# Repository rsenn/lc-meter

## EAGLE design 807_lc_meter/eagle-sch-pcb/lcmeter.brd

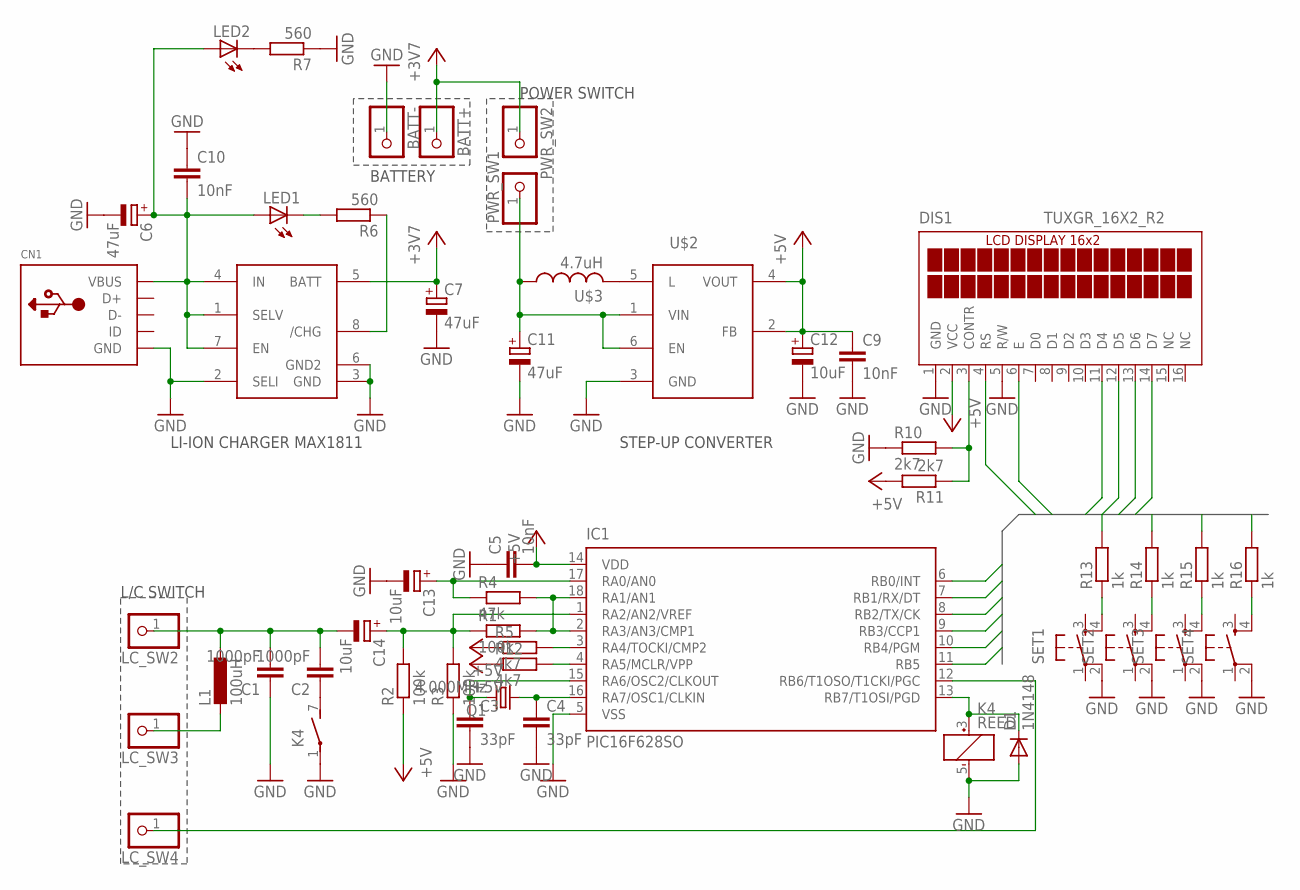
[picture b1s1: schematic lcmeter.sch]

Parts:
BATT+: PINHD-1X1; 1X01
BATT-: PINHD-1X1; 1X01
C1, C2: 1000pF; C0805
C3, C4: 33pF; C0805
C5, C9, C10: 10nF; C0805
C6, C7, C11: 47uF; B/3528-21W
C12, C13, C14: 10uF; B/3528-21W
CN1: USBMINIB; USB-MINIB
D1: 1N4148; MINIMELF
DIS1: TUXGR_16X2_R2
IC1: PIC16F628SO; SO-18W
K4: REED
L1: 100uH; 0204/5
LC_SW2, LC_SW3, LC_SW4: PINHD-1X1; 1X01
LED1, LED2: LED1206; LED-1206
PWR_SW1, PWR_SW2: PINHD-1X1; 1X01
Q1: 4.000MHz; CRYSTAL_SM49
R1, R2, R3: 100k; R0603
R4: 47k; R0603
R5, R12: 4k7; R0603
R6, R7: 560; R0603
R10, R11: 2k7; R0603
R13, R14, R15, R16: 1k; R0603
SET1, SET2, SET3, SET4: TAC_SWITCHPTH; TACTILE-PTH
U$1: MAX1811SO8; SO08
U$2: TPS6122XSOT-6; SOT23-6
U$3: 4.7uH; EPL3015

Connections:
+3V3: BATT+.1, C7.+, PWR_SW2.1, U$1.5 (BATT)
+5V: C5.2, C9.1, C12.+, DIS1.2 (VCC), IC1.14 (VDD), R2.1, R5.1, R11.2, R12.1, U$2.2 (FB), U$2.4 (VOUT)
GND: BATT-.1, C1.1, C3.2, C4.2, C5.1, C6.-, C7.-, C9.2, C10.1, C11.-, C12.-, C13.-, CN1.GND, D1.A, DIS1.1 (GND), DIS1.5 (R/W), IC1.5 (VSS), K4.1, K4.5 (-), R3.1, R7.1, R10.1, SET1.2, SET2.2, SET3.2, SET4.2, U$1.2 (SELI), U$1.3 (GND), U$1.6 (GND2), U$2.3 (GND)
LCDPIN0: DIS1.4 (RS), IC1.6 (RB0/INT)
LCDPIN1: DIS1.6 (E), IC1.7 (RB1/RX/DT)
LCDPIN2: DIS1.11 (D4), IC1.8 (RB2/TX/CK), R13.2
LCDPIN3: DIS1.12 (D5), IC1.9 (RB3/CCP1), R14.2
LCDPIN4: DIS1.13 (D6), IC1.11 (RB5), R15.2
LCDPIN5: DIS1.14 (D7), IC1.10 (RB4/PGM), R16.2
unnamed: C13.+, IC1.17 (RA0/AN0), R4.1
unnamed: IC1.2 (RA3/AN3/CMP1), IC1.18 (RA1/AN1), R1.2, R4.2
unnamed: C14.+, IC1.1 (RA2/AN2/VREF), R1.1, R2.2, R3.2
unnamed: C1.2, C2.2, C14.-, L1.1, LC_SW2.1
unnamed: DIS1.3 (CONTR), R10.2, R11.1
unnamed: C2.1, K4.7 (S)
unnamed: IC1.3 (RA4/TOCKI/CMP2), R5.2
unnamed: IC1.12 (RB6/T1OSO/T1CKI/PGC), LC_SW4.1
unnamed: C4.1, IC1.16 (RA7/OSC1/CLKIN), Q1.1
unnamed: C3.1, IC1.15 (RA6/OSC2/CLKOUT), Q1.2
unnamed: D1.C, IC1.13 (RB7/T1OSI/PGD), K4.3 (+)
unnamed: R13.1, SET1.4
unnamed: R14.1, SET2.4
unnamed: R15.1, SET3.4
unnamed: R16.1, SET4.4
unnamed: IC1.4 (RA5/MCLR/VPP), R12.2
unnamed: L1.2, LC_SW3.1
unnamed: C6.+, C10.2, CN1.VBUS, LED1.A, LED2.A, U$1.1 (SELV), U$1.4 (IN), U$1.7 (EN)
unnamed: U$2.5 (L), U$3.P$2 (2)
unnamed: LED1.C, R6.2
unnamed: R6.1, U$1.8 (/CHG)
unnamed: C11.+, PWR_SW1.1, U$2.1 (VIN), U$2.6 (EN), U$3.P$1 (1)
unnamed: LED2.C, R7.2

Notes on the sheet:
POWER SWITCH
BATTERY
L/C SWITCH
STEP-UP CONVERTER
LI-ION CHARGER MAX1811

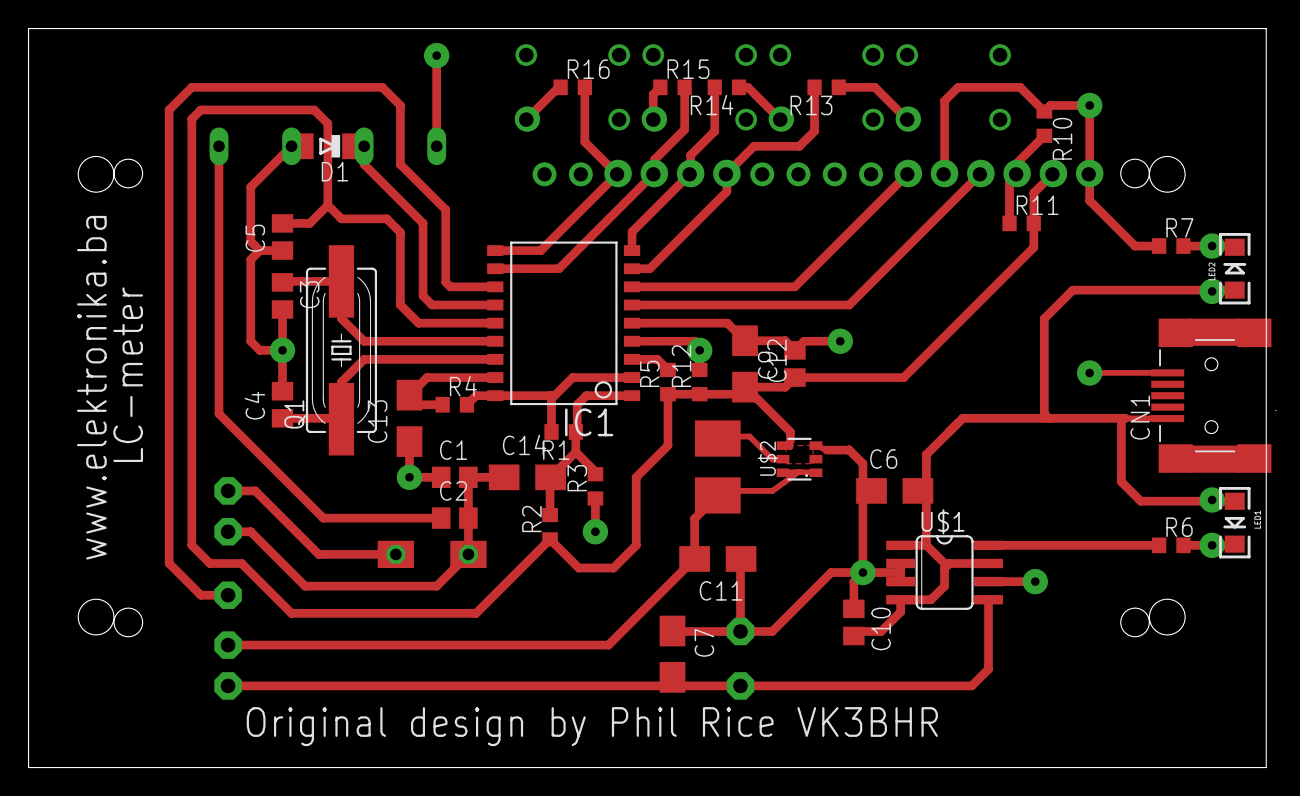
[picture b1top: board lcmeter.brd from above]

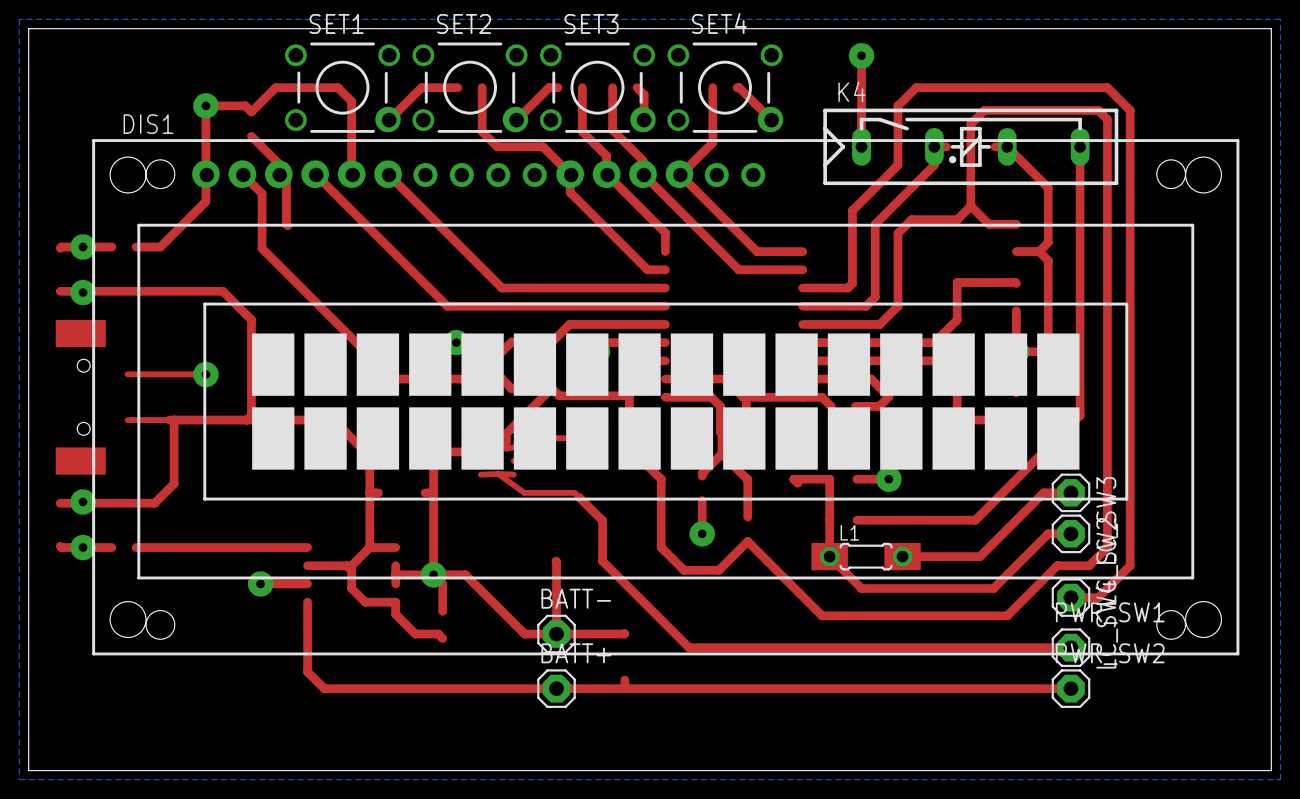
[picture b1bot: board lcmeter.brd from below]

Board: 2 copper layers, 86.7 x 51.7 mm, 50 parts (14 on the bottom side), 32 nets.

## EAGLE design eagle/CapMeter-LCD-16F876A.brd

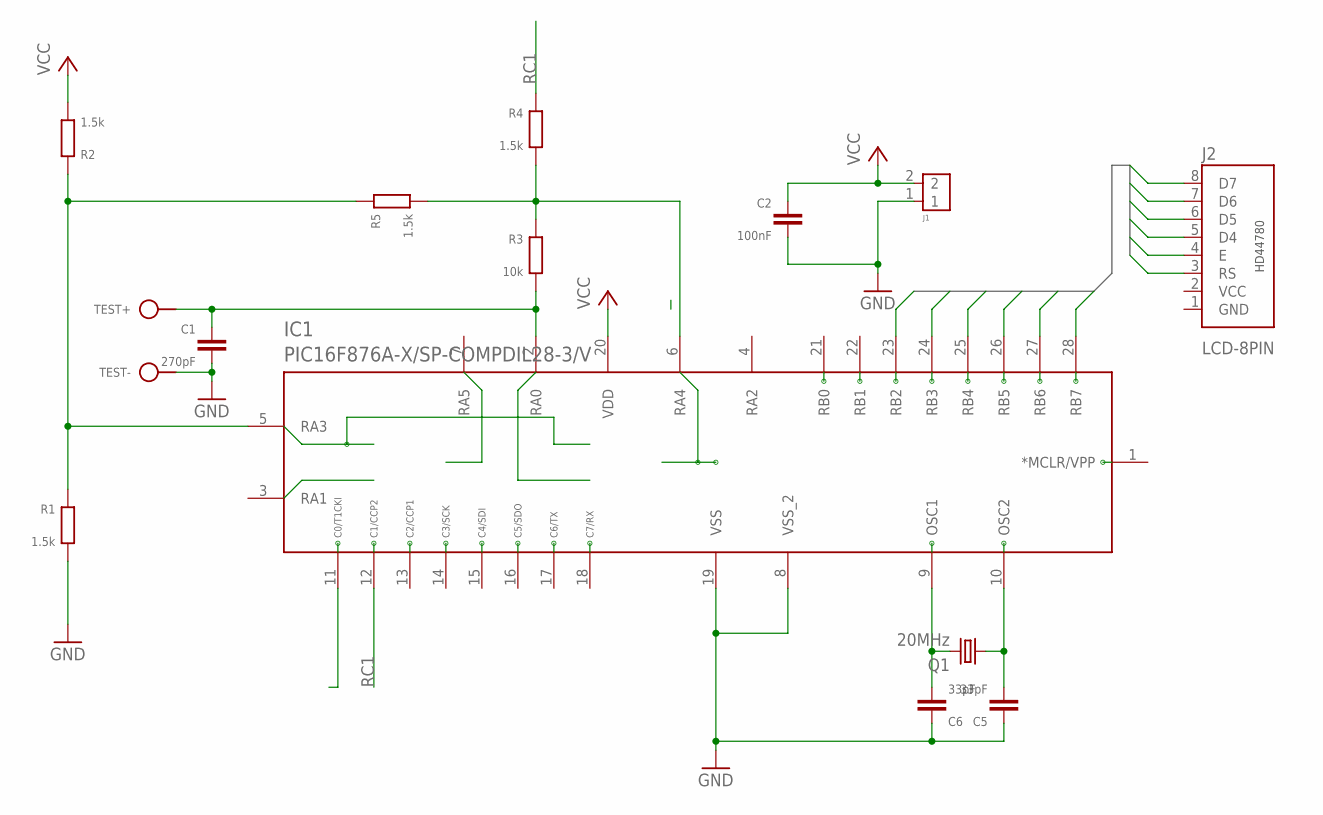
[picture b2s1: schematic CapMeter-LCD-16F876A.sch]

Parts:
C1: 270pF; C050-020X036
C2: 100nF; C025-020X036
C5, C6: 33pF; C025-020X036
IC1: PIC16F876A-X/SP-COMPDIL28-3/V; DIL28-3/V
J1: CONN-2P2P/H; CONN-2P
J2: LCD-8PIN; 1X8
Q1: 20MHz; HC49
R1, R2, R4, R5: 1.5k; 0204/10
R3: 10k; 0204/10
TEST+: SPAD
TEST-: SPAD

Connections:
D4: IC1.25 (RB4), J2.5 (D4)
D5: IC1.26 (RB5), J2.6 (D5)
D6: IC1.27 (RB6), J2.7 (D6)
D7: IC1.28 (RB7), J2.8 (D7)
E: IC1.24 (RB3), J2.4 (E)
GND: C1.2, C2.2, C5.1, C6.1, IC1.8 (VSS_2), IC1.19 (VSS), J1.1, R1.1, TEST-.1
unnamed: C1.1, IC1.2 (RA0), R3.1, TEST+.1
unnamed: IC1.6 (RA4), R3.2, R4.1, R5.1
unnamed: IC1.5 (RA3), R1.2, R2.2, R5.2
OSC1: C6.2, IC1.9 (OSC1), Q1.2
OSC2: C5.2, IC1.10 (OSC2), Q1.1
RC1: IC1.12 (RC1), R4.2
RS: IC1.23 (RB2), J2.3 (RS)
VCC: C2.1, IC1.20 (VDD), J1.2, R2.1

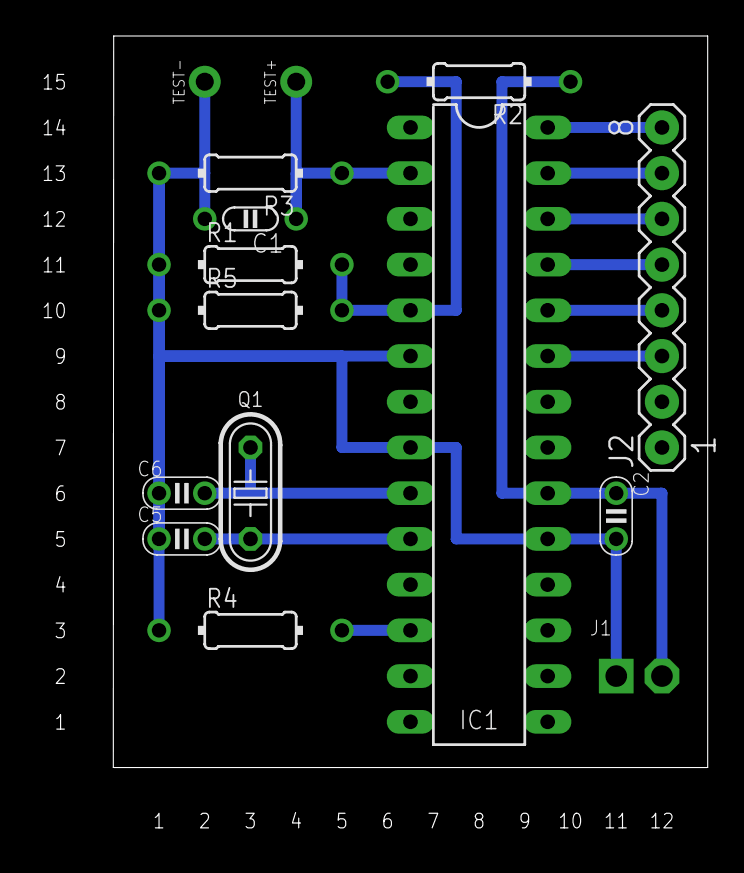
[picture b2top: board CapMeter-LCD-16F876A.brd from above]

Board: 2 copper layers, 33.0 x 40.6 mm, 15 parts (0 on the bottom side), 14 nets.

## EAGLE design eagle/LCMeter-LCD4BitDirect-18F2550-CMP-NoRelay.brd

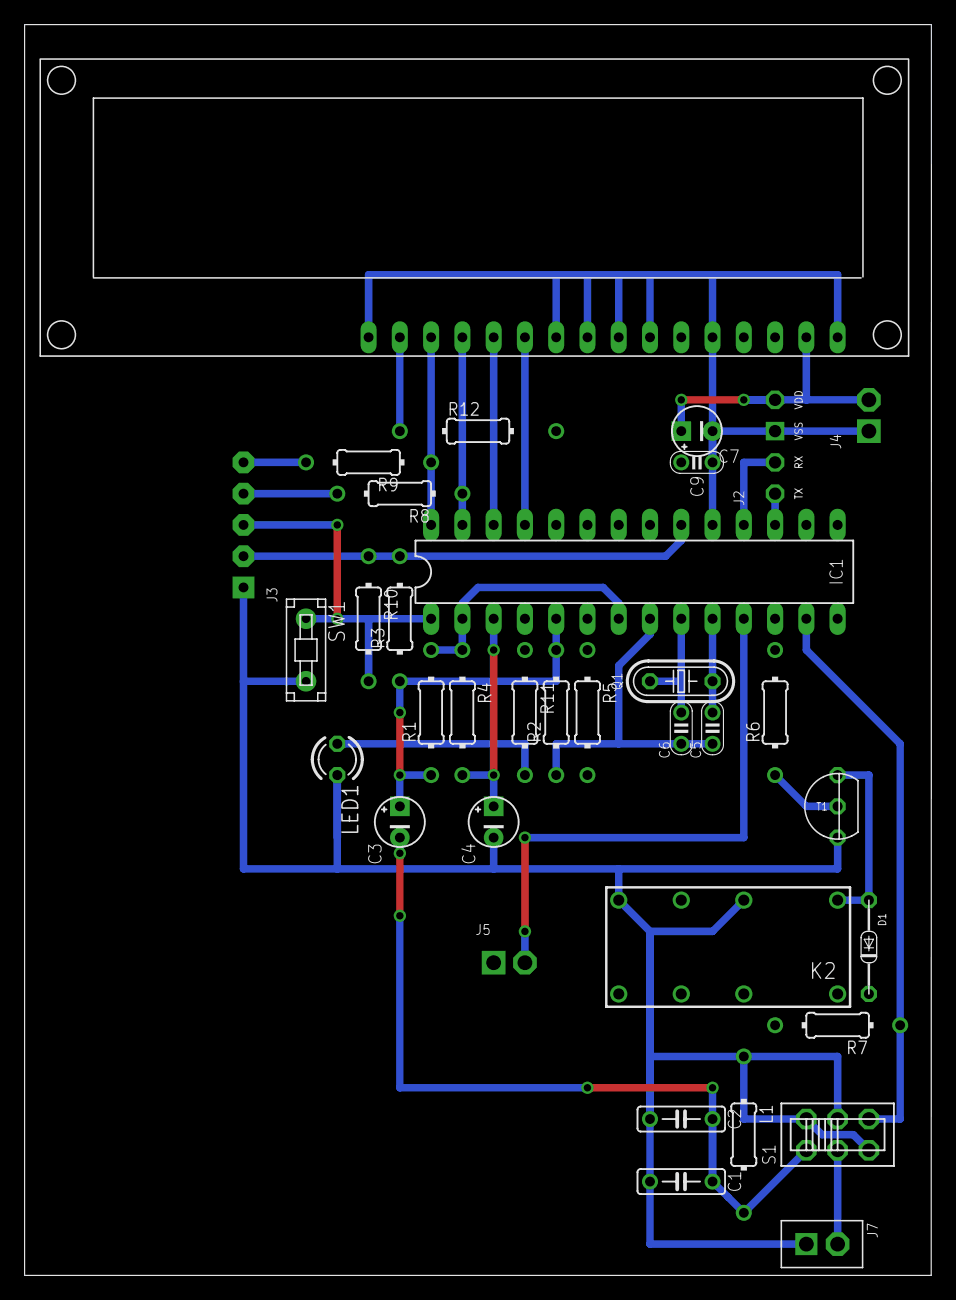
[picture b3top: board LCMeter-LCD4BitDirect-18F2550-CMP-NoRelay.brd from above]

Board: 2 copper layers, 73.7 x 101.6 mm, 35 parts (0 on the bottom side), 31 nets.

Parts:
C1, C2: 1nF; C050-025X060
C3, C4: 10μF; E2,5-4
C5, C6: 15pF; C025-020X036
C7: 100μF; E2,5-4
C9: 100nF; C025-020X036/V
D1: 1N4148; DO34-7
IC1: PIC18F2550-I/SP-COMP-B-V; DIL28-3/V
J2: PIC-UART
J3: PIC-ICSP
J4: PWR; CONN-2P
J5: FREQ; CONN-2P
J7: TEST-LC; CONN-2P-V
K2: DS2Y
L1: 82μH; 0204/12
LCD: HD44780LM016L; LM016L-HD44780
LED1: TLLG4400; LED3MM
Q1: 20MHz; HC49
R1, R2, R3: 100k; 0204/10
R4: 47k; 0204/10-V
R5, R10: 4.7k; 0204/10
R6, R7: 10k; 0204/10-V
R8, R9: 100; 0204/10-V
R11: 1k; 0204/10-V
R12: 330; 0204/12
S1: SL-SW-2P-2T; SLSW-2P2T
SW1: PB-1P-1T; PB-1P1T
T1: 2N3904; TO92

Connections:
/LC: IC1.13, R7.2, S1.6
/MCLR: IC1.1, J3.3, R10.2, SW1.2
/RELAY: IC1.12, R6.1
/RX: IC1.18, J2.18
/TX: IC1.17, J2.17
A0: IC1.2, IC1.7, R1.2, R4.2
A1: C4.+, IC1.3, R4.1
A3: C3.+, IC1.5, R1.1, R2.2, R3.1
A4: IC1.6, R5.1
C2_CON: C2.2, K2.4
D4: IC1.25, LCD.11
D5: IC1.26, LCD.12
D6: IC1.27, LCD.13, R8.2
D7: IC1.28, LCD.14, R9.2
E: IC1.24, LCD.6
FREQ: IC1.11, J5.2
GND: C1.2, C4.-, C5.1, C6.1, C7.-, C9.1, IC1.8, IC1.19, J2.19, J3.1, J4.1, J5.1, J7.1, K2.8, LCD.1, LCD.5, LCD.7, LCD.8, LCD.9, LCD.10, LCD.16, LED1.K, R2.1, S1.5, SW1.1, T1.1
IN+: J7.2, S1.2
unnamed: LED1.A, R11.1
unnamed: C1.1, C2.1, C3.-, L1.2, S1.1
unnamed: IC1.4, R11.2
unnamed: LCD.15, R12.1
unnamed: R6.2, T1.2
unnamed: L1.1, S1.3, S1.4
unnamed: D1.A, K2.1, T1.3
OSC1: C6.2, IC1.9, Q1.2
OSC2: C5.2, IC1.10, Q1.1
PGC: J3.4, R8.1
PGD: J3.5, R9.1
RS: IC1.23, LCD.4
VCC: C7.+, C9.2, D1.C, IC1.20, J2.20, J3.2, J4.2, K2.16, LCD.2, R3.2, R5.2, R7.1, R10.1, R12.2

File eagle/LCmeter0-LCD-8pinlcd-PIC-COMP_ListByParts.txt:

Part Value                   Attributes Package       Description                                                    Part Num,,
C1   1nF                                C050-025X060  CAPACITOR, European symbol                                     *       ,
C2   1nF                                C050-025X060  CAPACITOR, European symbol                                     *       ,
C3   10µF                               E2,5-4        POLARIZED CAPACITOR, European symbol                           *       
C4   10µF                               E2,5-4        POLARIZED CAPACITOR, European symbol                           *       
C5   33pF                               C025-020X036  CAPACITOR, European symbol                                     *       ,
C6   33pF                               C025-020X036  CAPACITOR, European symbol                                     *       ,
C7   100µF                              E2,5-5        POLARIZED CAPACITOR, European symbol                           *       
C8   22pF                               C050-020X036  CAPACITOR, European symbol                                     *       ,
C9   100nF                              C025-024X044  CAPACITOR, European symbol                                     *       ,
D1   1N4148                             DO34-7                                                                       *       ,,
D2   1N4148                             DO34-12V                                                                     *       ,,
IC1  PIC16F876A                         DIL28-3                                                                      *       ,,
J1   HD44780-4BITLCD44780-8P            CONN-LCD44780                                                                *       ,,
J2   PIC-UART                           PIC-UART                                                                     *       ,,
J3   PIC-ICSP                           PIC-ICSP                                                                     *       ,,
J4   J4                                 CONN-2P                                                                      *       ,,
J5   CONN-2P2P/V                        CONN-2P-V                                                                    *       ,,
J7   CONN-2P2P/V                        CONN-2P-V                                                                    *       ,,
K2   DS2Y                               DS2Y          MINIATURE RELAY NAiS                                           *       ,,
L1   68µH                               L-09R                                                                        *       ,,
LED1 TLLG4400                           LED3MM        Low Current (2mA) LED 3 mm Tinted Diffused Package color GREEN *       ,,
Q1   20MHz                              HC49                                                                         *       ,,
R1   100kO                              0202/7        RESISTOR, European symbol                                      *       ,
R2   100kO                              0202/7        RESISTOR, European symbol                                      *       ,
R3   100kO                              0202/7        RESISTOR, European symbol                                      *       ,
R4   47kO                               0202/7        RESISTOR, European symbol                                      *       ,
R5   4.7kO                              0202/7        RESISTOR, European symbol                                      *       ,
R6   10k                                0202/7-V      RESISTOR, European symbol                                      *       ,
R7   10kO                               0202/10       RESISTOR, European symbol                                      *       ,
R8   100                                0202/7        RESISTOR, European symbol                                      *       ,
R9   100                                0202/5-V      RESISTOR, European symbol                                      *       ,
R10  4.7kO                              0202/7        RESISTOR, European symbol                                      *       ,
R11  1k                                 0202/5-V      RESISTOR, European symbol                                      *       ,
S1   SL-SW-2P-2T-H                      SLSW-2P2T-H                                                                  *       ,,
SW1  PB-1P-1T                           PB-1P1T                                                                      *       ,,
T1   BC547                              TO92-CBE-A                                                                   *       ,,

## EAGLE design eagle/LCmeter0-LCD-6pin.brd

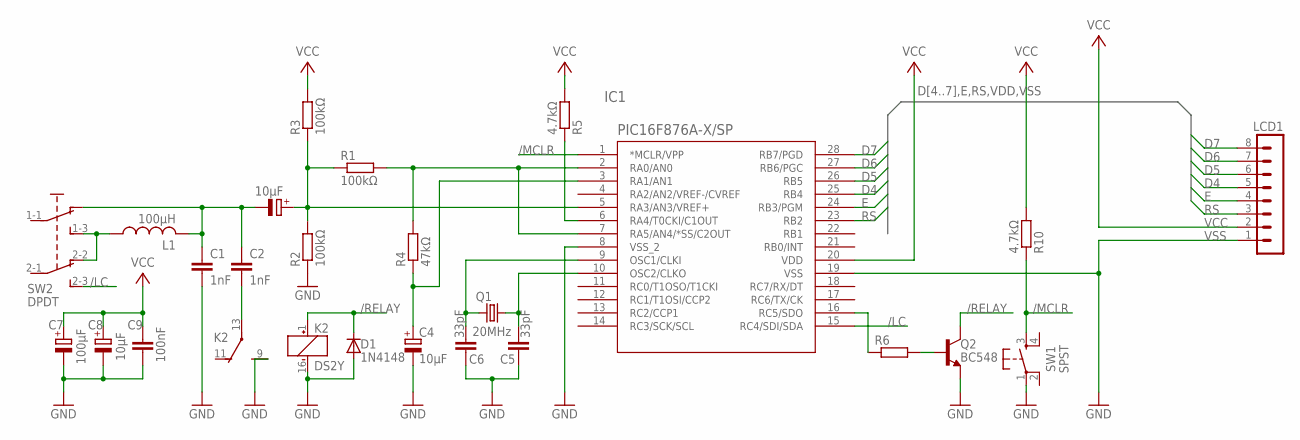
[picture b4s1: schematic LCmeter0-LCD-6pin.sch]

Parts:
C1, C2: 1nF; C050-025X075
C3: 10μF; E2,5-6
C4: 10μF; E5-6
C5, C6: 33pF; C050-025X075
C7: 100μF; E2,5-6
C8: 10μF; E2,5-5
C9: 100nF; C025-024X044
D1: 1N4148; DO35-7
IC1: PIC16F876A-X/SP; DIL28-3
K2: DS2Y
L1: 100μH; 0207/10
LCD1: MA08-1
Q1: 20MHz; HC49U70
Q2: BC548; TO92-EBC
R1, R2: 100kΩ; 0207/10
R3: 100kΩ; 0204V
R4: 47kΩ; 0207/10
R5, R10: 4.7kΩ; 0204V
R6: R-EU_0207/10; 0207/10
SW1: SPST; PB-5
SW2: DPDT

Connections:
/LC: IC1.15 (RC4/SDI/SDA), SW2.2-3
/MCLR: IC1.1 (*MCLR/VPP), R10.1, SW1.3 (S)
/RELAY: D1.C, K2.1 (+), Q2.C
A0: IC1.2 (RA0/AN0), IC1.7 (RA5/AN4/*SS/C2OUT), R1.2, R4.2
A1: C4.+, IC1.3 (RA1/AN1), R4.1
A3: C3.+, IC1.5 (RA3/AN3/VREF+), R1.1, R2.2, R3.1
A4: IC1.6 (RA4/T0CKI/C1OUT), R5.1
D4: IC1.25 (RB4), LCD1.5
D5: IC1.26 (RB5), LCD1.6
D6: IC1.27 (RB6/PGC), LCD1.7
D7: IC1.28 (RB7/PGD), LCD1.8
E: IC1.24 (RB3/PGM), LCD1.4
unnamed: C2.2, K2.13
unnamed: C1.1, C2.1, C3.-, L1.2, SW2.1-2
unnamed: Q2.B, R6.2
unnamed: L1.1, SW2.1-3, SW2.2-2
OSC1: C6.2, IC1.9 (OSC1/CLKI), Q1.1
OSC2: C5.2, IC1.10 (OSC2/CLKO), Q1.2
RC5: IC1.16 (RC5/SDO), R6.1
RS: IC1.23 (RB2), LCD1.3
VCC: C7.+, C8.+, C9.1, IC1.20 (VDD), LCD1.2, R3.2, R5.2, R10.2
VSS: C1.2, C4.-, C5.1, C6.1, C7.-, C8.-, C9.2, D1.A, IC1.8 (VSS_2), IC1.19 (VSS), K2.9 (S), K2.16 (-), LCD1.1, Q2.E, R2.1, SW1.1

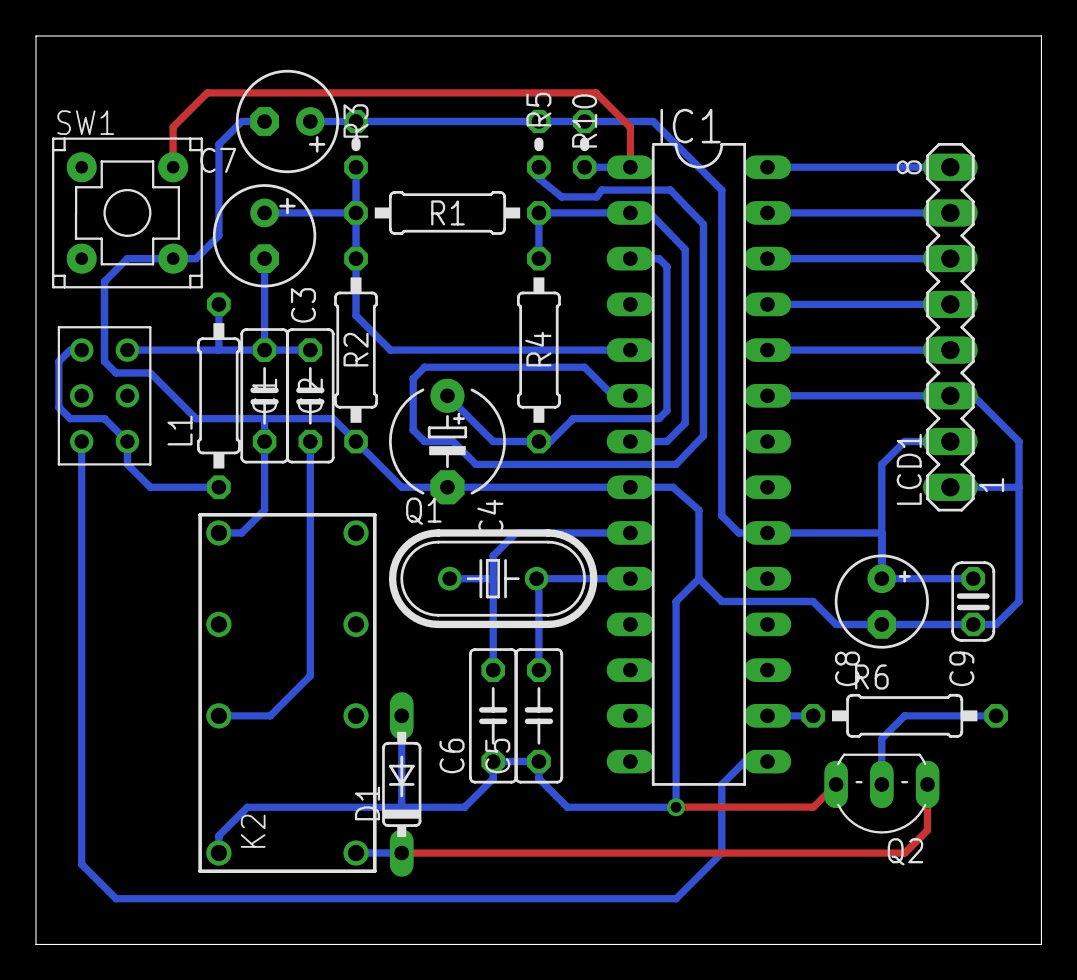
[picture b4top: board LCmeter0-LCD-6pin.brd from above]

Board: 2 copper layers, 55.9 x 50.5 mm, 25 parts (0 on the bottom side), 22 nets.

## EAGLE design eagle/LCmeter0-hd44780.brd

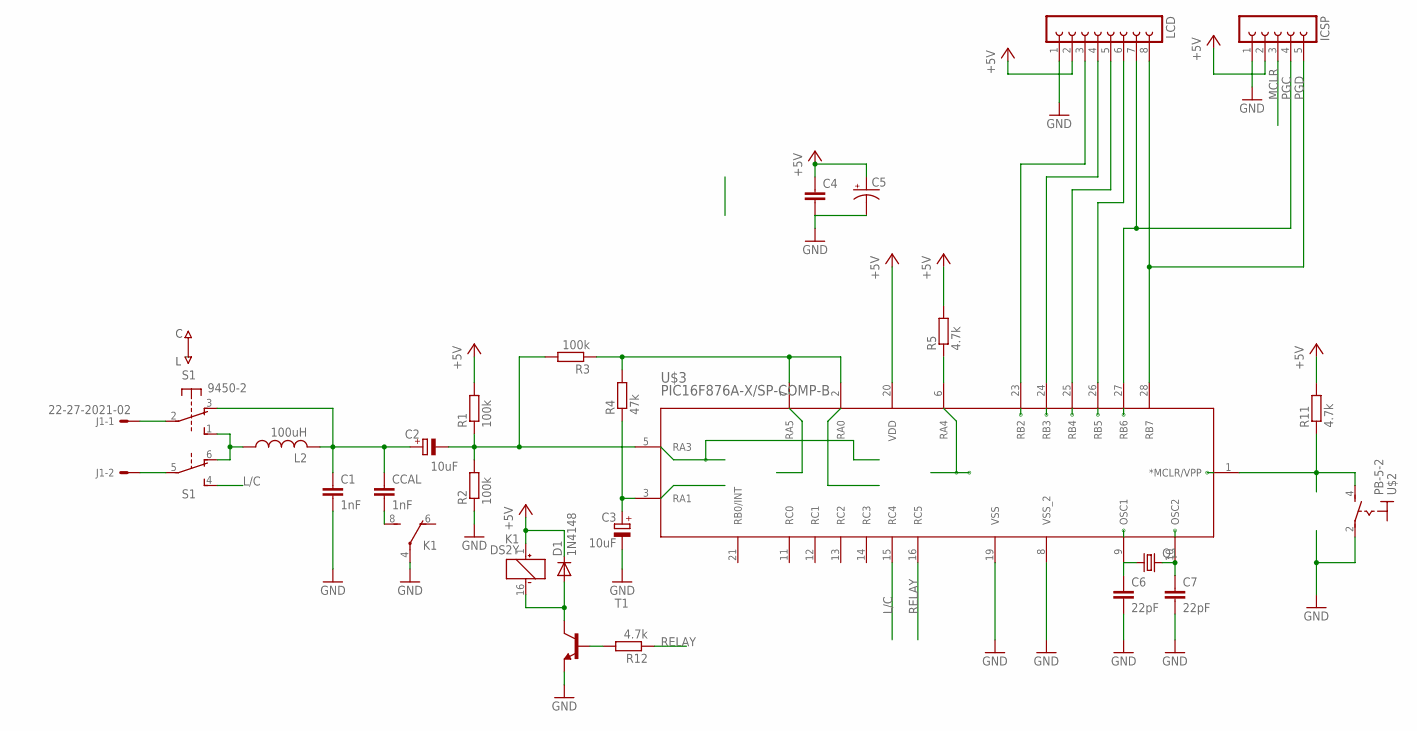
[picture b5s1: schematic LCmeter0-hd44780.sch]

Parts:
C1: 1nF; C050-025X075
C2: 10uF; E5-4
C3: 10uF; E5-5
C4: C-EU025-024X044; C025-024X044
C5: CPOL-USE2,5-6E; E2,5-6E
C6, C7: 22pF; C050-024X044
CCAL: 1nF; C050-025X075
D1: 1N4148; DO35-7
ICSP: FE05-1
J1: 22-27-2021-02; 6410-02
K1: DS2Y
L2: 100uH; 0204/7
LCD: FE08-1; FE08
Q1: CRYSTALHC49S; HC49/S
R1, R2: 100k; 0204V
R3: 100k; 0204/7
R4: 47k; 0204V
R5: 4.7k; 0204/5
R11: 4.7k; 0204V
R12: 4.7k; 0207/10
S1: 9450-2
T1: BC548-NPN-TO92-CBE; TO92-CBE
U$2: PB-5-2; PB-5-1
U$3: PIC16F876A-X/SP-COMP-B; DIL28-3

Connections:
+5V: C4.1, C5.+, D1.C, ICSP.2, K1.1 (+), LCD.2, R1.2, R5.2, R11.2, U$3.20 (VDD)
GND: C1.2, C3.-, C4.2, C5.-, C6.2, C7.2, ICSP.1, K1.4, R2.1, T1.E, U$2.2, U$3.8 (VSS_2), U$3.19 (VSS)
L/C: S1.4 (S), U$3.15 (RC4)
MCLR: ICSP.3, R11.1, U$2.4 (S), U$3.1 (*MCLR/VPP)
unnamed: LCD.3, U$3.23 (RB2)
unnamed: LCD.4, U$3.24 (RB3)
unnamed: LCD.5, U$3.25 (RB4)
unnamed: LCD.6, U$3.26 (RB5)
unnamed: J1.1, S1.2
unnamed: R5.1, U$3.6 (RA4)
unnamed: J1.2, S1.5
unnamed: C7.1, Q1.2, U$3.10 (OSC2)
unnamed: C6.1, Q1.1, U$3.9 (OSC1)
unnamed: R3.1, R4.2, U$3.2 (RA0), U$3.7 (RA5)
unnamed: R12.2, T1.B
unnamed: D1.A, K1.16 (-), T1.C
unnamed: CCAL.2, K1.8 (S)
unnamed: C1.1, C2.+, CCAL.1, L2.2, S1.3 (O)
unnamed: L2.1, S1.1 (S), S1.6 (O)
PGC: ICSP.4, LCD.7, U$3.27 (RB6)
PGD: ICSP.5, LCD.8, U$3.28 (RB7)
RA1: C3.+, R4.1, U$3.3 (RA1)
RA3: C2.-, R1.1, R2.2, R3.2, U$3.5 (RA3)
RELAY: R12.1, U$3.16 (RC5)

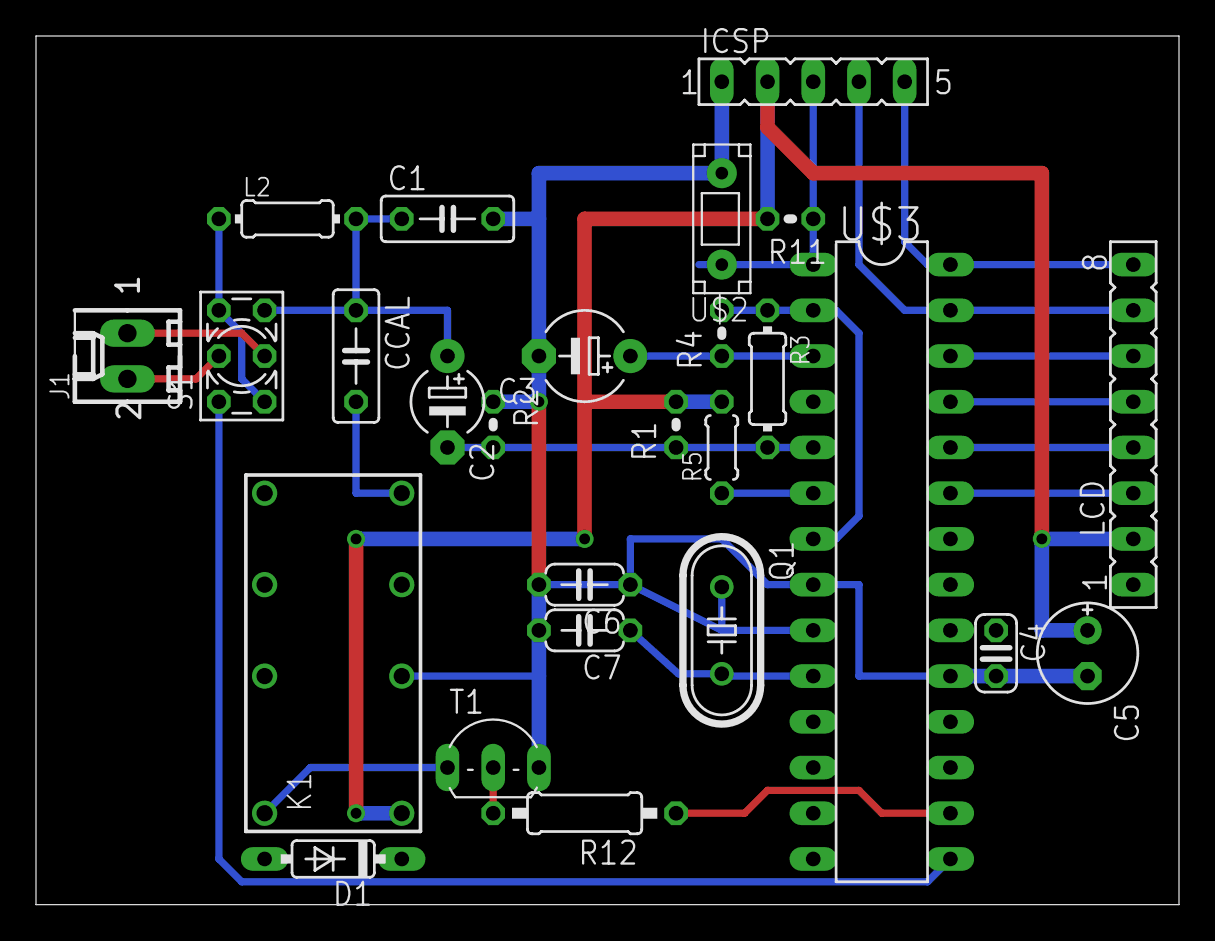
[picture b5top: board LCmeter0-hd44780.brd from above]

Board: 2 copper layers, 63.5 x 48.3 mm, 26 parts (0 on the bottom side), 24 nets.

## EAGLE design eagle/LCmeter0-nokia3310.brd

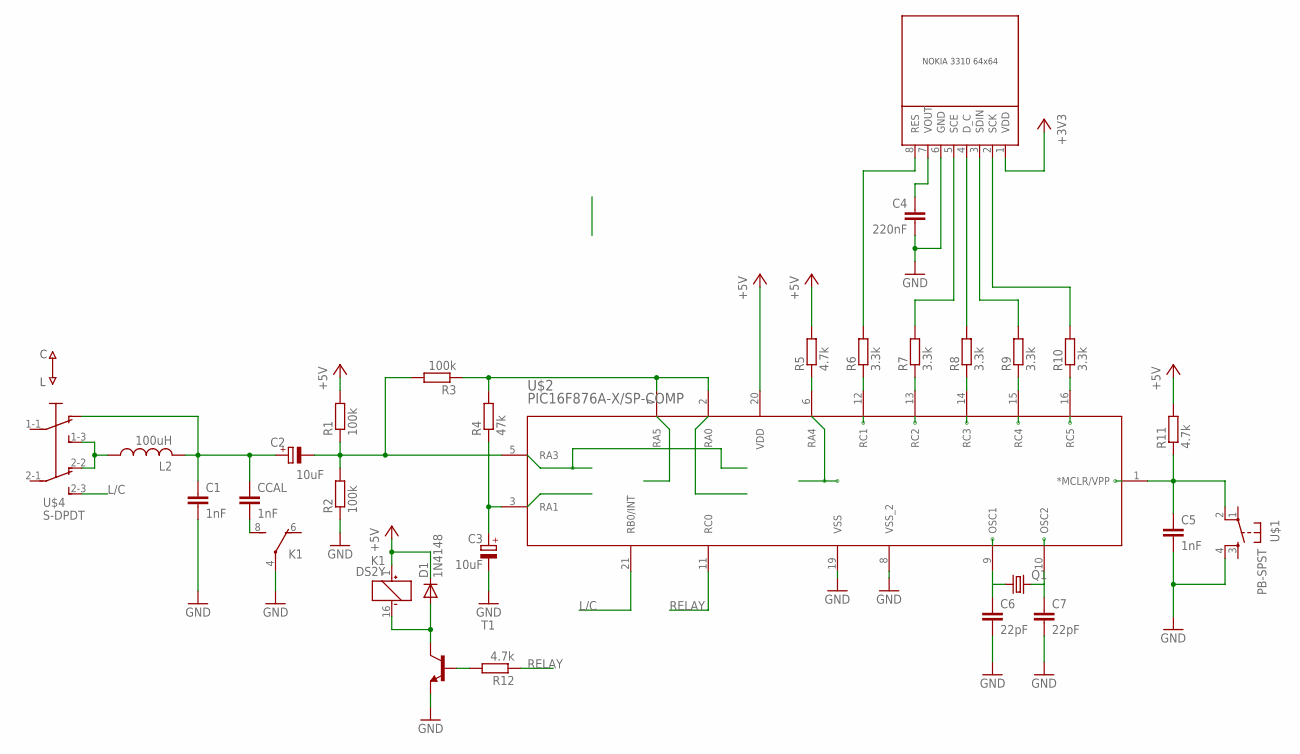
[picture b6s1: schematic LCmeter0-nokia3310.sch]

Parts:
C1, C5: 1nF; C050-025X075
C2, C3: 10uF; E2,5-5
C4: 220nF; C050-025X075
C6, C7: 22pF; C050-025X075
CCAL: 1nF; C050-025X075
D1: 1N4148; DO35-7
K1: DS2Y
L2: 100uH; IR-2
Q1: CRYSTALHC49S; HC49/S
R1, R3: 100k; 0204/7
R2: 100k; 0204V
R4: 47k; 0204V
R5, R12: 4.7k; 0204/7
R6, R7, R8, R9, R10: 3.3k; 0207/10
R11: 4.7k; 0204V
T1: BC548-NPN-TO92-CBE; TO92-CBE
U$1: PB-SPST; PB-5
U$2: PIC16F876A-X/SP-COMP; DIL28-3
U$3: NOKIA-3310-64X64; 1X8
U$4: S-DPDT; DPDT

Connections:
+3V3: U$3.1 (VDD)
+5V: D1.C, K1.1 (+), R1.2, R5.2, R11.2, U$2.20 (VDD)
GND: C1.2, C3.-, C4.2, C5.2, C6.2, C7.2, K1.4, R2.1, T1.E, U$1.4 (S1), U$2.8 (VSS_2), U$2.19 (VSS), U$3.6 (GND)
L/C: U$2.21 (RB0/INT), U$4.2-3
unnamed: R6.1, U$2.12 (RC1)
unnamed: R7.1, U$2.13 (RC2)
unnamed: R8.1, U$2.14 (RC3)
unnamed: R9.1, U$2.15 (RC4)
unnamed: R10.1, U$2.16 (RC5)
unnamed: R5.1, U$2.6 (RA4)
unnamed: C5.1, R11.1, U$1.2 (P1), U$2.1 (*MCLR/VPP)
unnamed: C7.1, Q1.2, U$2.10 (OSC2)
unnamed: C6.1, Q1.1, U$2.9 (OSC1)
unnamed: R10.2, U$3.2 (SCK)
unnamed: R9.2, U$3.3 (SDIN)
unnamed: R8.2, U$3.4 (D_C)
unnamed: R7.2, U$3.5 (SCE)
unnamed: R6.2, U$3.8 (RES)
unnamed: C4.1, U$3.7 (VOUT)
unnamed: R3.1, R4.2, U$2.2 (RA0), U$2.7 (RA5)
unnamed: R12.2, T1.B
unnamed: D1.A, K1.16 (-), T1.C
unnamed: CCAL.2, K1.8 (S)
unnamed: C1.1, C2.+, CCAL.1, L2.2, U$4.1-2
unnamed: L2.1, U$4.1-3, U$4.2-2
RA1: C3.+, R4.1, U$2.3 (RA1)
RA3: C2.-, R1.1, R2.2, R3.2, U$2.5 (RA3)
RELAY: R12.1, U$2.11 (RC0)

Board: 2 copper layers, 29 parts (0 on the bottom side), 27 nets.
